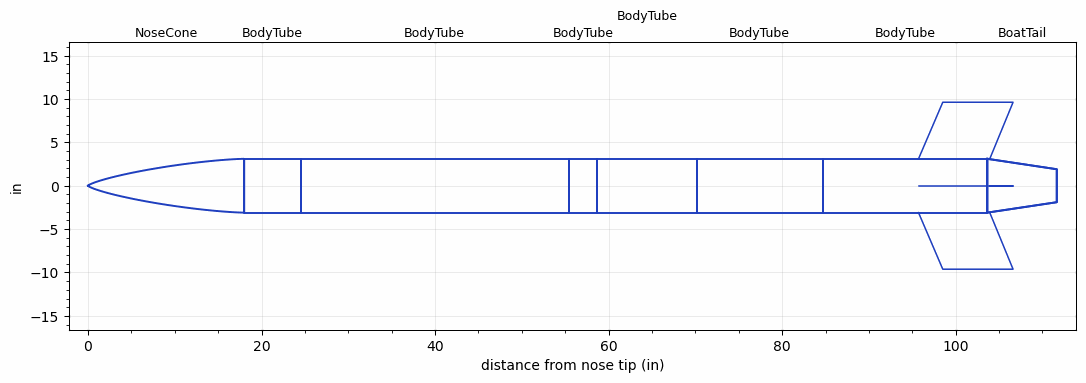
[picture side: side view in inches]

<RASAeroDocument>
 <FileVersion>2</FileVersion>
 <RocketDesign>
  <NoseCone>
   <Length>18</Length>
   <Diameter>6.2</Diameter>
   <Shape>Von Karman Ogive</Shape>
   <Location>0</Location>
  </NoseCone>
  <BodyTube>
   <Length>6.5</Length>
   <Diameter>6.2</Diameter>
   <Location>18</Location>
  </BodyTube>
  <BodyTube>
   <Length>30.8999</Length>
   <Diameter>6.2</Diameter>
   <Location>24.5</Location>
  </BodyTube>
  <BodyTube>
   <Length>3.25</Length>
   <Diameter>6.2</Diameter>
   <Location>55.3999</Location>
  </BodyTube>
  <BodyTube>
   <Length>11.5</Length>
   <Diameter>6.2</Diameter>
   <Location>58.6499</Location>
  </BodyTube>
  <BodyTube>
   <Length>14.5</Length>
   <Diameter>6.2</Diameter>
   <Location>70.1499</Location>
  </BodyTube>
  <BodyTube>
   <Length>19</Length>
   <Diameter>6.2</Diameter>
   <RailGuideDiameter>0.621</RailGuideDiameter>
   <RailGuideHeight>0.684</RailGuideHeight>
   <Location>84.6499</Location>
   <BoattailLength>8</BoattailLength>
   <BoattailRearDiameter>3.8</BoattailRearDiameter>
   <Overhang>0.2790003</Overhang>
   <Fin>
    <Count>4</Count>
    <Chord>8.213</Chord>
    <Span>6.52</Span>
    <SweepDistance>2.795</SweepDistance>
    <TipChord>8.1</TipChord>
    <Thickness>0.2</Thickness>
    <Location>7.934</Location>
    <AirfoilSection>Rounded</AirfoilSection>
   </Fin>
  </BodyTube>
  <BoatTail>
   <Length>8</Length>
   <Diameter>6.2</Diameter>
   <RearDiameter>3.8</RearDiameter>
   <Location>103.6499</Location>
  </BoatTail>
  <Surface>Sheet Metal</Surface>
  <ModifiedBarrowman>False</ModifiedBarrowman>
  <Turbulence>False</Turbulence>
  <UseBooster1>False</UseBooster1>
  <UseBooster2>False</UseBooster2>
 </RocketDesign>
 <LaunchSite>
  <Altitude>2871</Altitude>
  <Pressure>28.9938</Pressure>
  <RodAngle>6</RodAngle>
  <RodLength>154.9997</RodLength>
  <Temperature>86</Temperature>
  <WindSpeed>1.5882</WindSpeed>
 </LaunchSite>
 <Recovery>
  <Altitude1>1476</Altitude1>
  <Altitude2>656.168</Altitude2>
  <DeviceType1>Parachute</DeviceType1>
  <DeviceType2>Parachute</DeviceType2>
  <Event1>True</Event1>
  <Event2>True</Event2>
  <Size1>95.9998</Size1>
  <Size2>35.9999</Size2>
  <EventType1>Altitude</EventType1>
  <EventType2>Apogee</EventType2>
  <CD1>1.35</CD1>
  <CD2>0</CD2>
 </Recovery>
 <SimulationList>
  <Simulation>
   <SustainerLaunchWt>62.6506</SustainerLaunchWt>
   <SustainerCG>67.971</SustainerCG>
   <SustainerIgnitionDelay>0</SustainerIgnitionDelay>
   <Booster1SeparationDelay>0</Booster1SeparationDelay>
   <Booster1IgnitionDelay>0</Booster1IgnitionDelay>
   <IncludeBooster1>False</IncludeBooster1>
   <Booster2Delay>0</Booster2Delay>
   <IncludeBooster2>False</IncludeBooster2>
  </Simulation>
 </SimulationList>
</RASAeroDocument>
